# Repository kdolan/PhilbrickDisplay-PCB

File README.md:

# PhilbrickDisplay-PCB
Printed Circuit Board for the Computer Science House Philbrick Scrolling LED Display

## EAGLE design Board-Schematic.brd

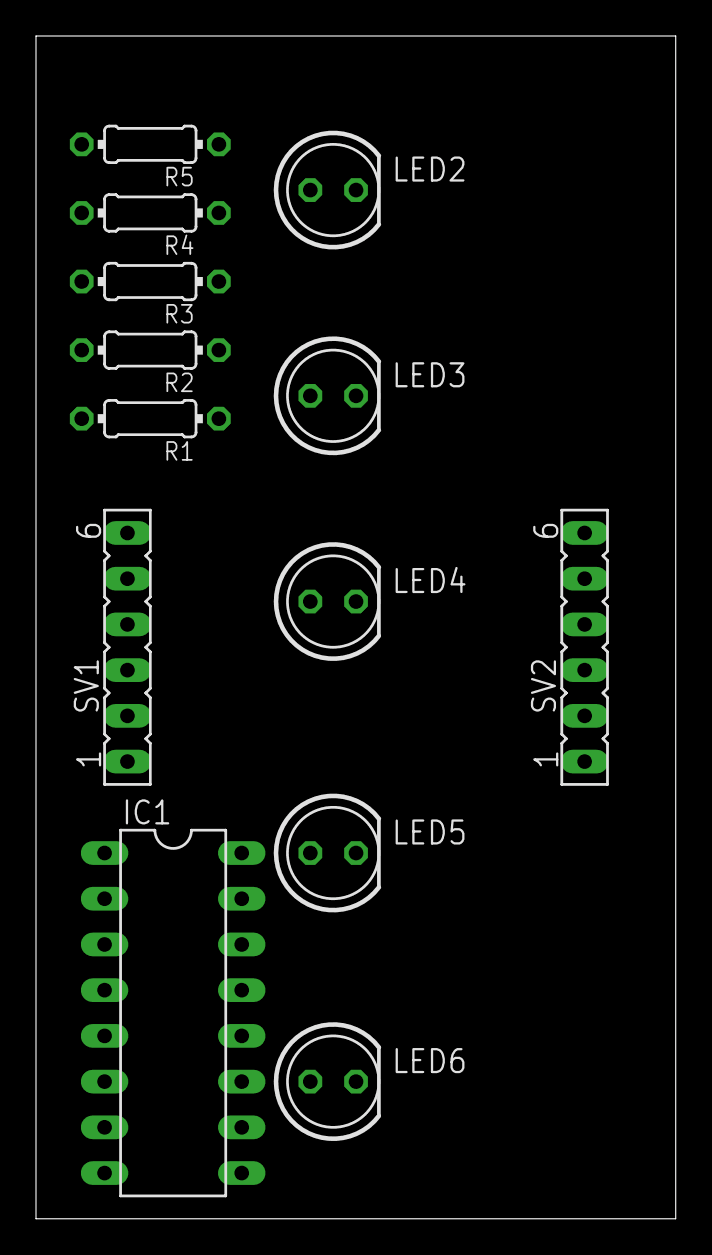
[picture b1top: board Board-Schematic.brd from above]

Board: 2 copper layers, 35.5 x 65.7 mm, 13 parts (0 on the bottom side), 17 nets, no tracks yet.

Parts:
IC1: 74HC595N; DIL16
LED2, LED3, LED4, LED5, LED6: LED5MM
R1, R2, R3, R4, R5: 0204/7
SV1, SV2: FE06

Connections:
A: IC1.15, LED2.A
B: IC1.1, LED3.A
C: IC1.2, LED4.A
CLK: IC1.11, SV1.3, SV2.3
D: IC1.3, LED5.A
DATA-IN: IC1.14, SV1.2
DATA-OUT: IC1.9, SV2.2
E: IC1.4, LED6.A
GND: IC1.8, IC1.13, R1.2, R5.2, SV1.6, SV2.6
LATCH: IC1.12, SV1.4, SV2.4
unnamed: LED2.K, R1.1
unnamed: LED3.K, R2.1
unnamed: LED4.K, R3.1
unnamed: LED5.K, R4.1
unnamed: LED6.K, R5.1
RESET: IC1.10, SV1.5, SV2.5
VCC: IC1.16, SV1.1, SV2.1

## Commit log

2015-01-29 Adds schematic file
2015-01-30 Schematic and quick board layout
2015-01-30 Rename board and schematic.
